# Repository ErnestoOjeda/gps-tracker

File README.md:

# wander-hardware

### Overview

The Wander v1.1 prototype is an adaptation of the Particle LTE line of industrialized cellular IoT modules. It is based on the Particle E-Series LTE module and includes an onboard GPS module based on the MTK-3339 chipset.

### Description

#### Front

#### Back

| ID 					    | Description                                      |
|:--------------------------|:-------------------------------------------------|
| **LiPo Battery Contacts**        | This is directly connected to the LIPO pin. The recommended input voltage range on this pin is between 3.6V to 4.4VDC. Make sure that the battery can handle currents of at least 3Amp.  |
| **PA6H GPS module**           |MTK-3339-based GPS module that can track up to 22 satellites on 66 channels, with an excellent -165 dB sensitivity receiver, and a built in antenna.|
| **GPS FIX LED**     | This LED blinks at about 1Hz while it's searching for satellites and blinks once every 15 seconds when a fix is found to conserve power.|
| **Charge status LED**     | Pretty self-explanatory.|
| **RGB LED**        | Displays cellular connectivity status.|
| **u-blox cell module**    | This is the u-blox SARA module.|
| **uFl antenna connector** |Plug the antenna here. |
| **E Module USB port**       | This is the module's microUSB port that connects to the STM32F microcontroller.|

### Components List

* u-blox SARA R410M LTE modem
  * LTE CAT M1/ NB1 module with global hardware support
  * 3GPP Release 13 LTE Cat M1
* MediaTek MTK3339
  * SBAS, Galileo, GLONASS, GPS / QZSS
  * Supports WAAS/EGNOS/MSAS/GAGAN
  * 22 tracking / 66 acquisition-channel GPS receiver
* STMElectronics LSM303ADRTR
  * 3 magnetic field channels and 3 acceleration channels
  * Embedded temperature sensor
* STMicroelectronics STM32F205RGT6 
  * 120MHz ARM Cortex M3 microcontroller
  * 1MB flash, 128KB RAM 
  * Supports DSP instructions, hardware accelerated FPU calculations 
* MAX17043 fuel gauge
* Micro USB 2.0 full speed (12 Mbps)
* FCC and PTCRB certified
* RoHS compliant (lead-free)

### Structure of this Repository
 - /bom
     + Contains the electronics bill of materials outlining the components used
 - /cad-cases
     + Contains .f3d files for various looks-like/works-like case designs
 - /datasheets
     + Contains the relevant datasheets of the components used
 - /documentation
     + Contains prototype PRD and Working Specification & Requirements sheets
 - /eagle
     + Contains the schematic and PCB files in the Eagle file format
 - /gerbers
     + Contains PCB gerber files for manufacturing
 - /images
     + Contains the images used in the description

### Change Log
#### v1.1.0 (LATEST)
* initial beta release

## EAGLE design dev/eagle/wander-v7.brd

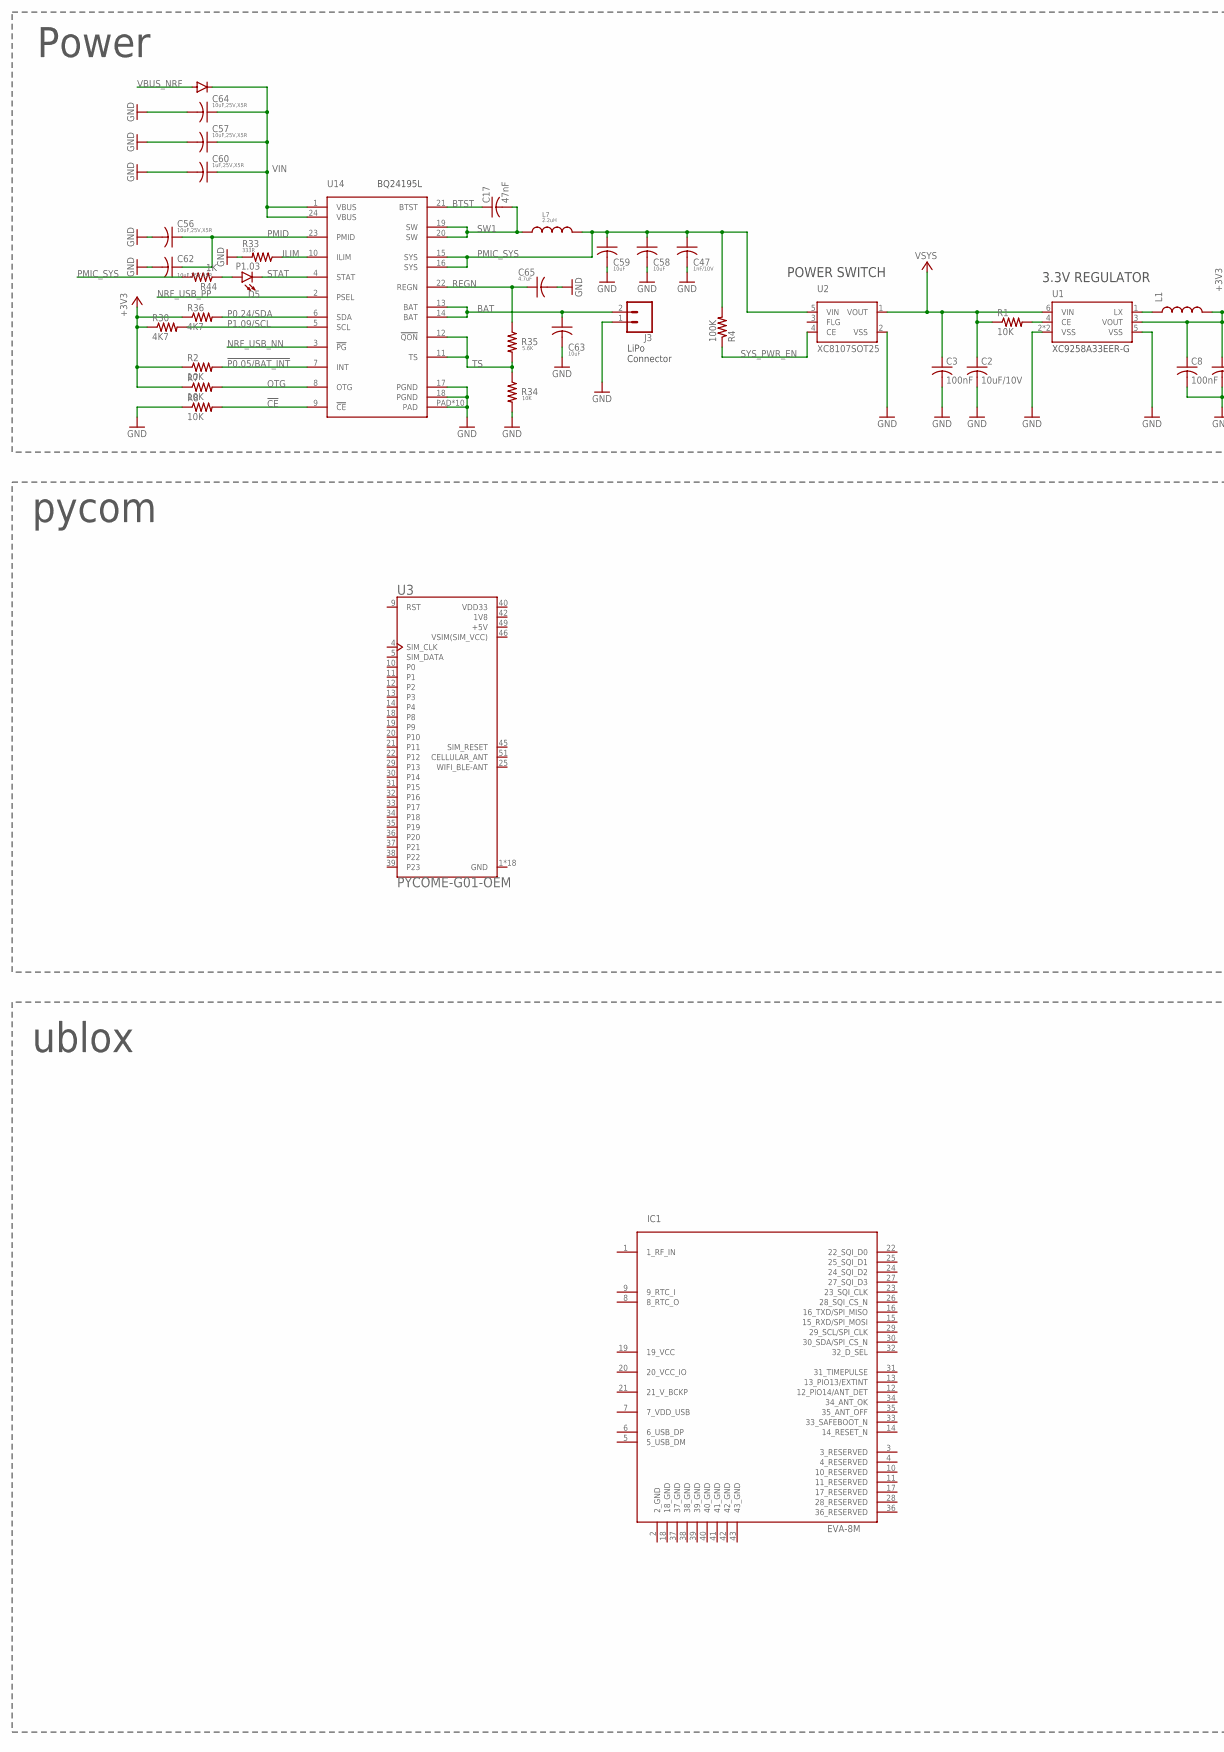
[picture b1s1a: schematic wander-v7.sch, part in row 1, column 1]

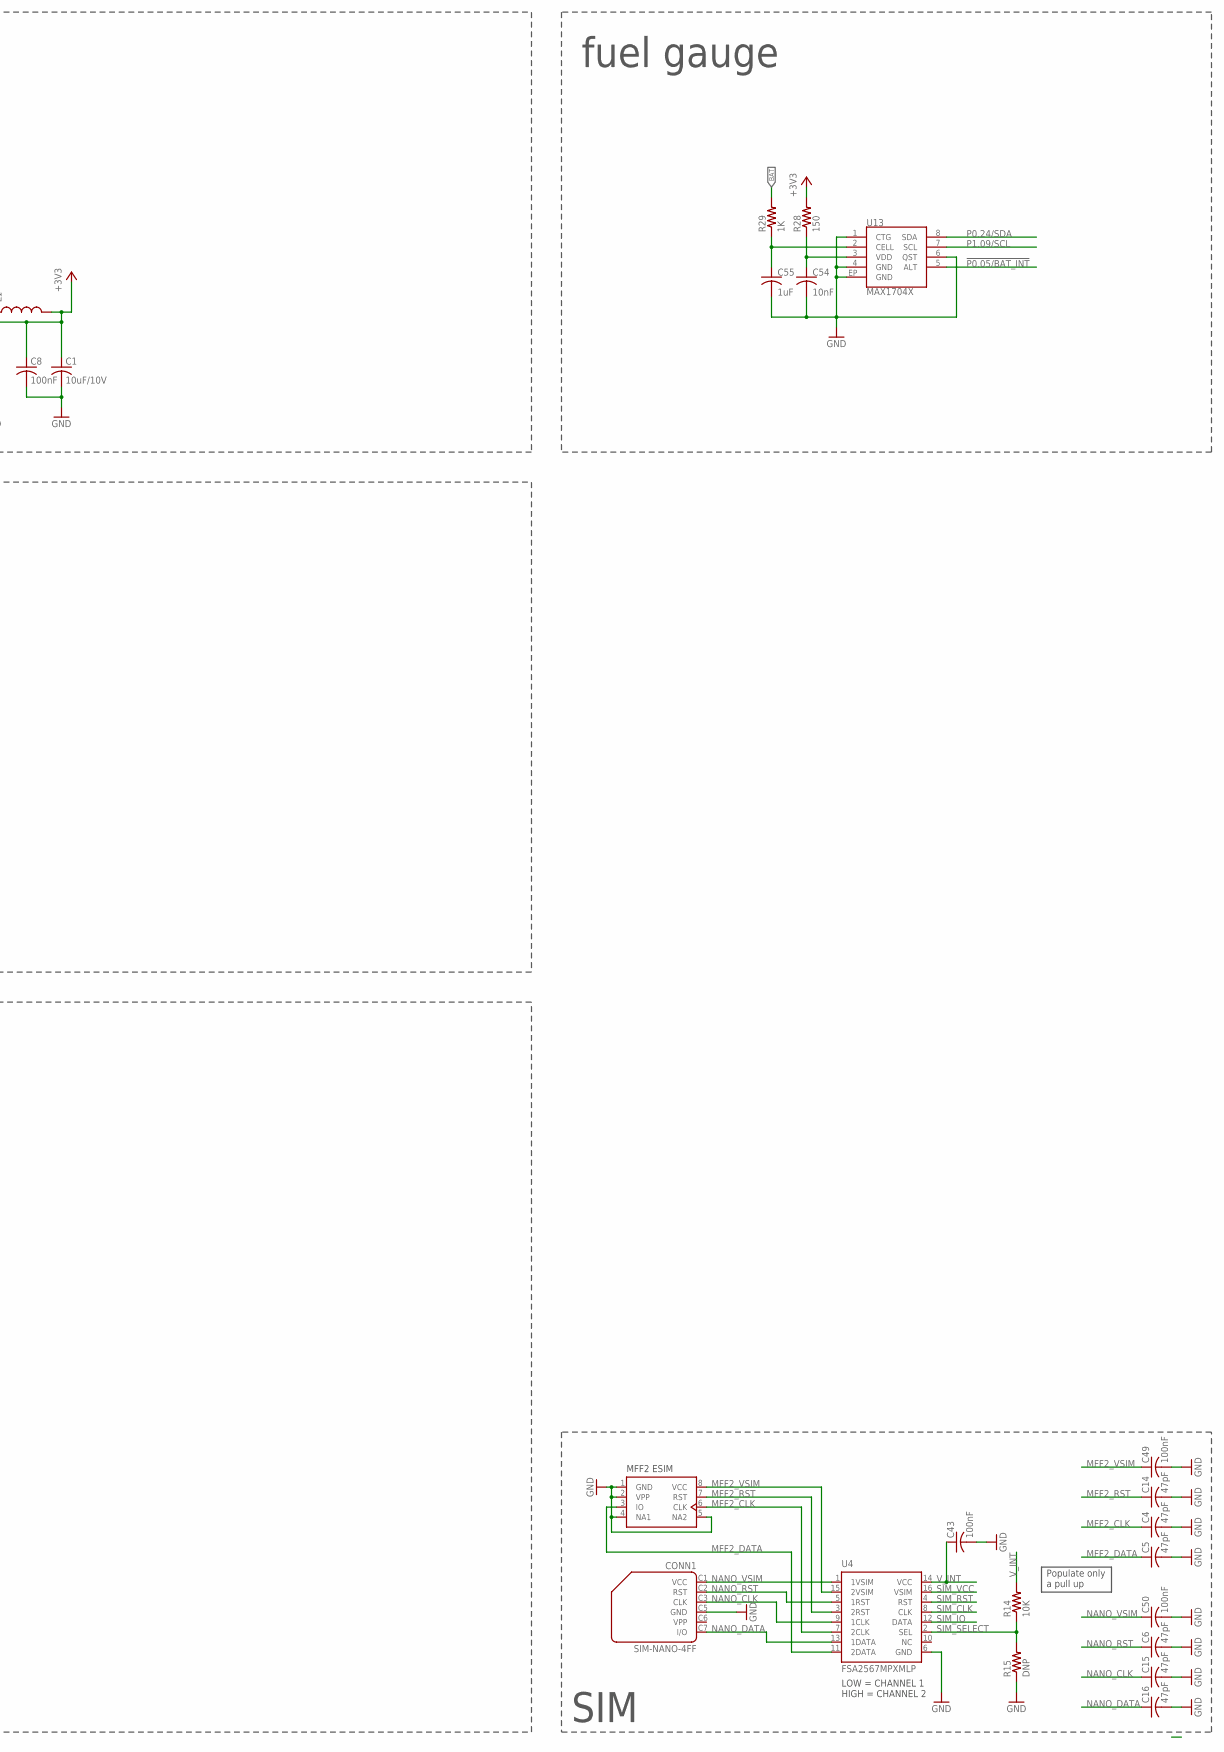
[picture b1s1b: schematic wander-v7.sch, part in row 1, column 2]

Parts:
C1, C2: 10uF/10V; C0603K
C3: 100nF; C0603K
C4, C5, C6, C14, C15, C16: 47pF; C0201_B
C8, C43, C49, C50: 100nF; C0201_B
C17: 47nF; C0201_B
C47: 1nF/10V; C0402_B
C54: 10nF; C0402_B
C55: 1uF; C0402_B
C56, C57, C62, C64: 10uF,25V,X5R; C0603_B
C58, C59, C63: 10uF; C0603_B
C60: 1uF,25V,X5R; C0603_B
C65: 4.7uF; C0603_B
CONN1: SIM-NANO-4FF; GCT-SIM8100
D4: DIODE_NT; DIODE-DO-220AA_NT(SMP)
D5: P1.03; LED-0603
IC1: EVA-8M
J3: CONN_02-JST-2MM-SMT; JST-2-SMD@2
L1: INDUCTOR-SPARKFUNVLS3012ET-4R7M; INDUCTOR-VLS-E
L7: 2.2uH; INDUCTOR-4040
R1, R2, R7, R8, R14: 10K; C0201_B
R4: 100K; C0201_B
R15: DNP; C0201_B
R28: 150; 0402-RES
R29: 1K; 0402-RES
R30, R36: 4K7; C0201_B
R33: 333R; R0402_B
R34: 10K; R0402_B
R35: 5.6K; R0402_B
R44: 1K; C0201_B
U1: XC9258A33EER-G; USP-6C
U2: XC8107SOT25; SOT25
U3: PYCOME-G01-OEM; PYCOM_PYCOME-G01-OEM
U4: FSA2567MPXMLP; MLP16
U7: ESIMSON8; MFF2
U13: MAX1704X; TDFN-8
U14: BQ24195L; QFN24

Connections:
1V8: U3.42 (1V8)
!CE: R8.2, U14.9 (!CE)
!P0.05/BAT_INT: R2.2, U13.5 (ALT), U14.7 (INT)
+3V3: C1.1, C8.1, L1.P$2 (2), R2.1, R7.1, R28.2, R30.1, R36.1, U1.3 (VOUT)
+5V: U3.49 (+5V)
BAT: C63.1, J3.2 (1), R29.2, U14.13 (BAT), U14.14 (BAT)
BTST: C17.1, U14.21 (BTST)
GND: C1.2, C2.2, C3.2, C4.2, C5.2, C6.2, C8.2, C14.2, C15.2, C16.2, C43.2, C47.2, C49.2, C50.2, C54.2, C55.2, C56.2, C57.2, C58.2, C59.2, C60.2, C62.2, C63.2, C64.2, C65.2, CONN1.C5 (GND), J3.1 (2), R8.1, R15.1, R33.2, R34.2, U1.2 (VSS), U1.5 (VSS), U1.P$1 (VSS), U2.2 (VSS), U3.1 (GND), U3.2 (GND), U3.3 (GND), U3.6 (GND), U3.7 (GND), U3.8 (GND), U3.23 (GND), U3.24 (GND), U3.26 (GND), U3.27 (GND), U3.28 (GND), U3.41 (GND), U3.43 (GND), U3.44 (GND), U3.47 (GND), U3.48 (GND), U3.50 (GND), U3.52 (GND), U4.6 (GND), U7.1 (GND), U7.2 (VPP), U7.4 (NA1), U7.5 (NA2), U13.1 (CTG), U13.4 (GND), U13.6 (QST), U13.EP (GND), U14.17 (PGND), U14.18 (PGND), U14.PAD, U14.PAD@1 (PAD), U14.PAD@2 (PAD), U14.PAD@3 (PAD), U14.PAD@4 (PAD), U14.PAD@5 (PAD), U14.PAD@6 (PAD), U14.PAD@7 (PAD), U14.PAD@8 (PAD), U14.PAD@9 (PAD)
ILIM: R33.1, U14.10 (ILIM)
MFF2_CLK: C4.1, U4.7 (2CLK), U7.6 (CLK)
MFF2_DATA: C5.1, U4.11 (2DATA), U7.3 (IO)
MFF2_RST: C14.1, U4.3 (2RST), U7.7 (RST)
MFF2_VSIM: C49.1, U4.15 (2VSIM), U7.8 (VCC)
unnamed: D5.A, R44.1
unnamed: R1.2, U1.4 (CE)
unnamed: L1.P$1 (1), U1.1 (LX)
unnamed: C54.1, R28.1, U13.3 (VDD)
unnamed: C55.1, R29.1, U13.2 (CELL)
NANO_CLK: C15.1, CONN1.C3 (CLK), U4.9 (1CLK)
NANO_DATA: C16.1, CONN1.C7 (I/O), U4.13 (1DATA)
NANO_RST: C6.1, CONN1.C2 (RST), U4.5 (1RST)
NANO_VSIM: C50.1, CONN1.C1 (VCC), U4.1 (1VSIM)
NRF_USB_NN: U14.3 (!PG)
NRF_USB_PP: U14.2 (PSEL)
OTG: R7.2, U14.8 (OTG)
P0.24/SDA: R36.2, U13.8 (SDA), U14.6 (SDA)
P1.09/SCL: R30.2, U13.7 (SCL), U14.5 (SCL)
PMIC_SYS: C47.1, C58.1, C59.1, L7.P$2 (2), R4.2, R44.2, U2.5 (VIN), U14.15 (SYS), U14.16 (SYS)
PMID: C56.1, C62.1, U14.23 (PMID)
REGN: C65.1, R35.1, U14.22 (REGN)
SIM_CLK: U4.8 (CLK)
SIM_IO: U4.12 (DATA)
SIM_RST: U4.4 (RST)
SIM_SELECT: R14.1, R15.2, U4.2 (SEL)
SIM_VCC: U4.16 (VSIM)
STAT: D5.C, U14.4 (STAT)
SW1: C17.2, L7.P$1 (1), U14.19 (SW), U14.20 (SW)
SYS_PWR_EN: R4.1, U2.4 (CE)
TS: R34.1, R35.2, U14.11 (TS), U14.12 (!QON)
VBUS_NRF: D4.ANODE
VDD33: U3.40 (VDD33)
VIN: C57.1, C60.1, C64.1, D4.CATHODE, U14.1 (VBUS), U14.24 (VBUS)
VSIM(SIM_VCC): U3.46 (VSIM(SIM_VCC))
VSYS: C2.1, C3.1, R1.1, U1.6 (VIN), U2.1 (VOUT)
V_INT: C43.1, R14.2, U4.14 (VCC)

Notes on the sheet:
MFF2 ESIM
Populate only a pull up
3.3V REGULATOR
LiPo Connector
ublox
pycom
Power
SIM
fuel gauge
LOW = CHANNEL 1 HIGH = CHANNEL 2
POWER SWITCH

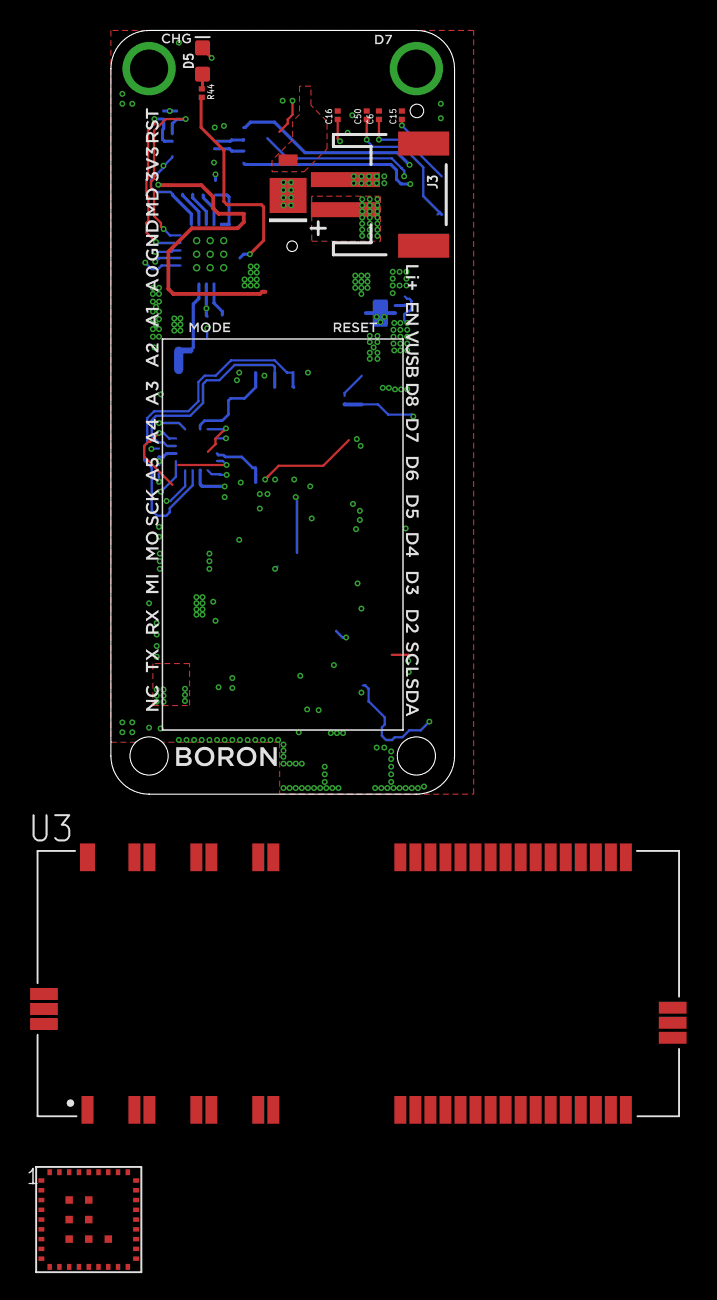
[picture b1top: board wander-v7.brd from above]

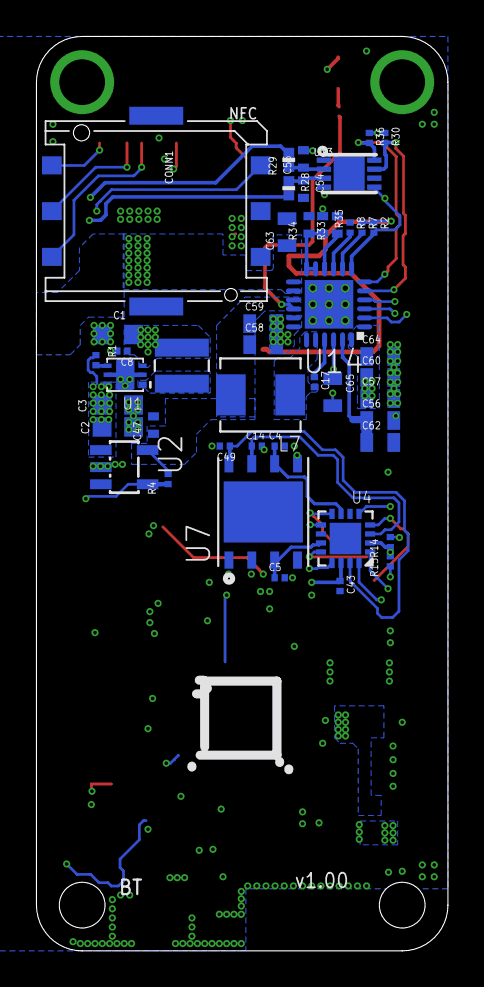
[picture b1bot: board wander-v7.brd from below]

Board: 8 copper layers, 22.9 x 50.8 mm, 55 parts (45 on the bottom side), 34 nets.

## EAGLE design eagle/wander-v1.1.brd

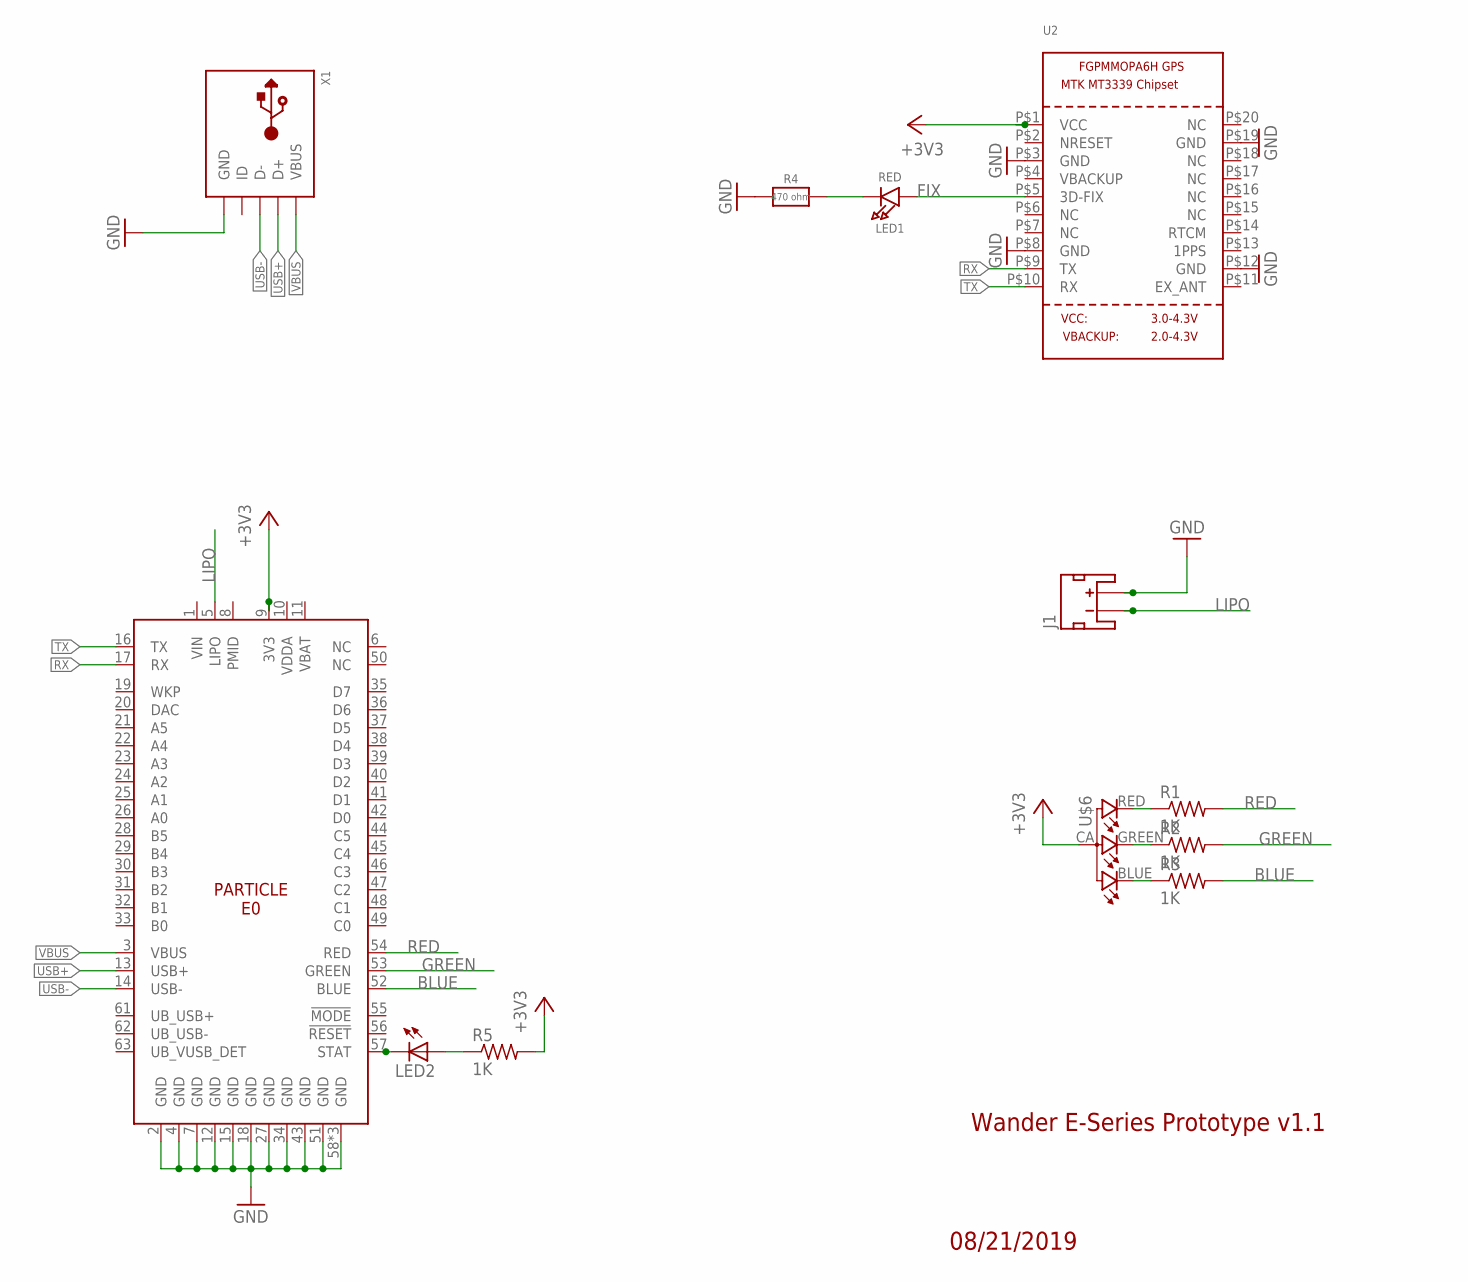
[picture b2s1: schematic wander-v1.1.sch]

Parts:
J1: JST_2MM_MALE; JST-2-SMD
LED1: RED; CHIPLED_0805_NOOUTLINE
LED2: LED0603; LED-0603
R1, R2, R3, R5: 1K; R0603
R4: 470 ohm; 0805-NO
U1: E0_V005; E0
U2: GPS_FGPMMOPA6H; FGPMMOPA6H
U$6: RGB-LED-CLMVB-FKARGB; PLCC4-2MM-RGB
X1: USB-NEW-PHOTON; 4UCONN_CMCUSB-5BFM14X-01-X

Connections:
+3V3: R5.2, U1.9 (3V3), U2.P$1 (VCC), U$6.CA (1)
BLUE: R3.2, U1.52 (BLUE)
FIX: LED1.A, U2.P$5 (3D-FIX)
GND: J1.2 (+), R4.1, U1.2 (GND), U1.4 (GND), U1.7 (GND), U1.12 (GND), U1.15 (GND), U1.18 (GND), U1.27 (GND), U1.34 (GND), U1.43 (GND), U1.51 (GND), U1.58 (GND), U1.59 (GND), U1.60 (GND), U2.P$3 (GND), U2.P$8 (GND), U2.P$12 (GND), U2.P$19 (GND), X1.P$1 (GND), X1.P$6 (GND), X1.P$7 (GND), X1.P$8 (GND), X1.P$9 (GND), X1.P$10 (GND), X1.P$11 (GND)
GREEN: R2.2, U1.53 (GREEN)
LIPO: J1.1 (-), U1.5 (LIPO)
unnamed: R1.1, U$6.RED (4)
unnamed: R2.1, U$6.GREEN (3)
unnamed: R3.1, U$6.BLUE (2)
unnamed: LED1.C, R4.2
unnamed: LED2.A, R5.1
unnamed: LED2.C, U1.57 (STAT)
RED: R1.2, U1.54 (RED)
RX: U1.17 (RX), U2.P$9 (TX)
TX: U1.16 (TX), U2.P$10 (RX)
USB+: U1.13 (USB+), X1.P$3 (D+)
USB-: U1.14 (USB-), X1.P$4 (D-)
VBUS: U1.3 (VBUS), X1.P$5 (VBUS)

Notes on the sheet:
08/21/2019
Wander E-Series Prototype v1.1

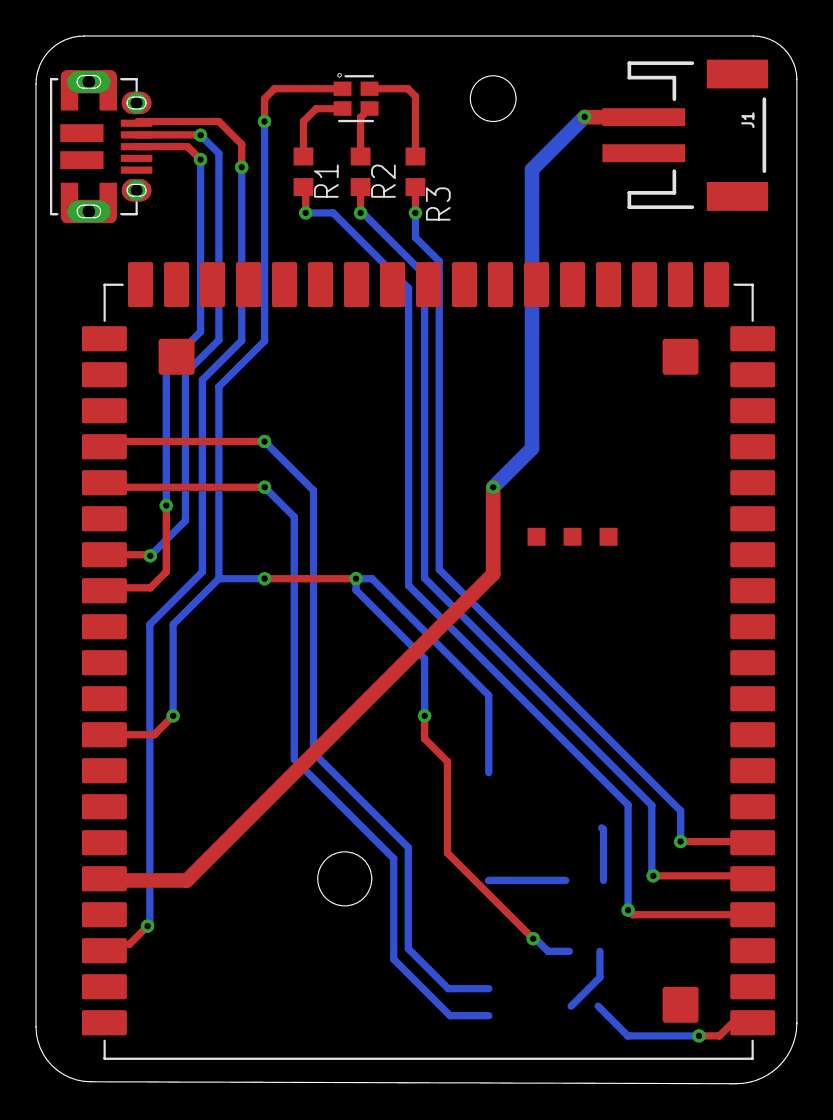
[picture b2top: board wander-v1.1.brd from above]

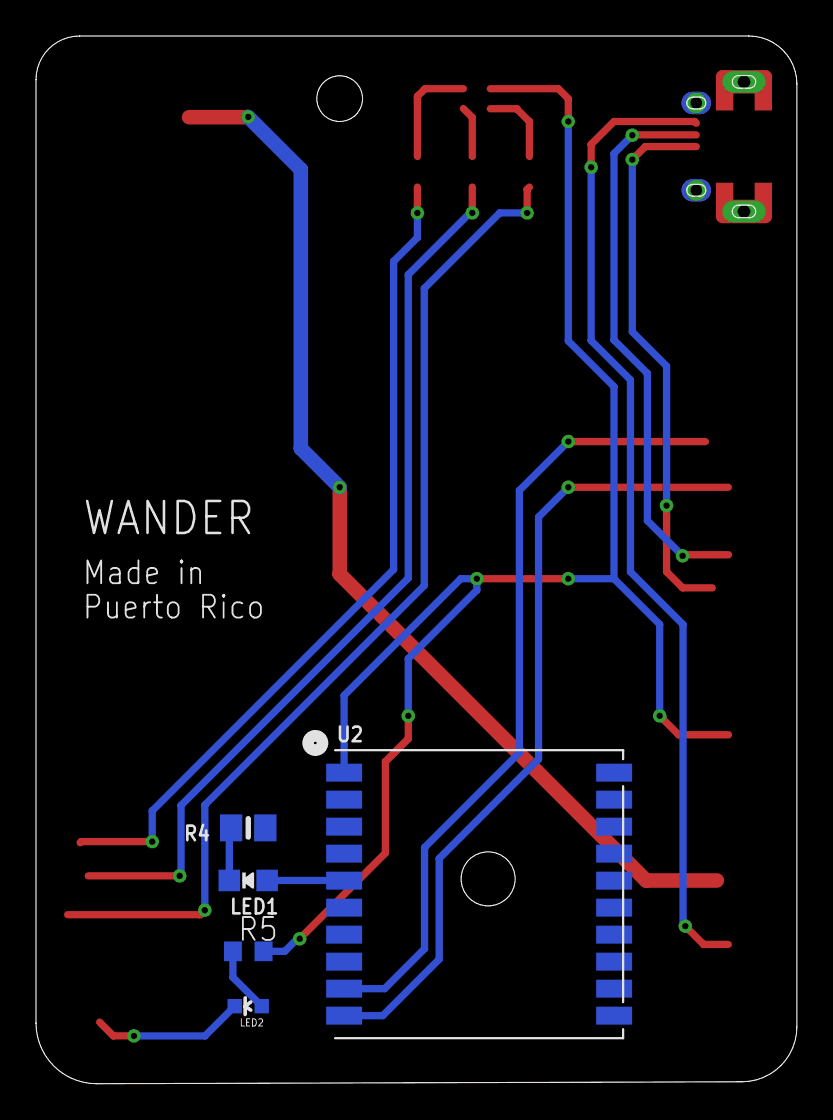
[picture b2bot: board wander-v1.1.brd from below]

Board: 2 copper layers, 42.3 x 58.2 mm, 12 parts (5 on the bottom side), 18 nets.

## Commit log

2019-11-04 new changes

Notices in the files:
parts and their libraries:
SparkFun-Connectors: Licensing: Creative Commons ShareAlike 4.0 International - https://creativecommons.org/licenses/by-sa/4.0
Particle-Devices: Licensing: Designed by Particle.
